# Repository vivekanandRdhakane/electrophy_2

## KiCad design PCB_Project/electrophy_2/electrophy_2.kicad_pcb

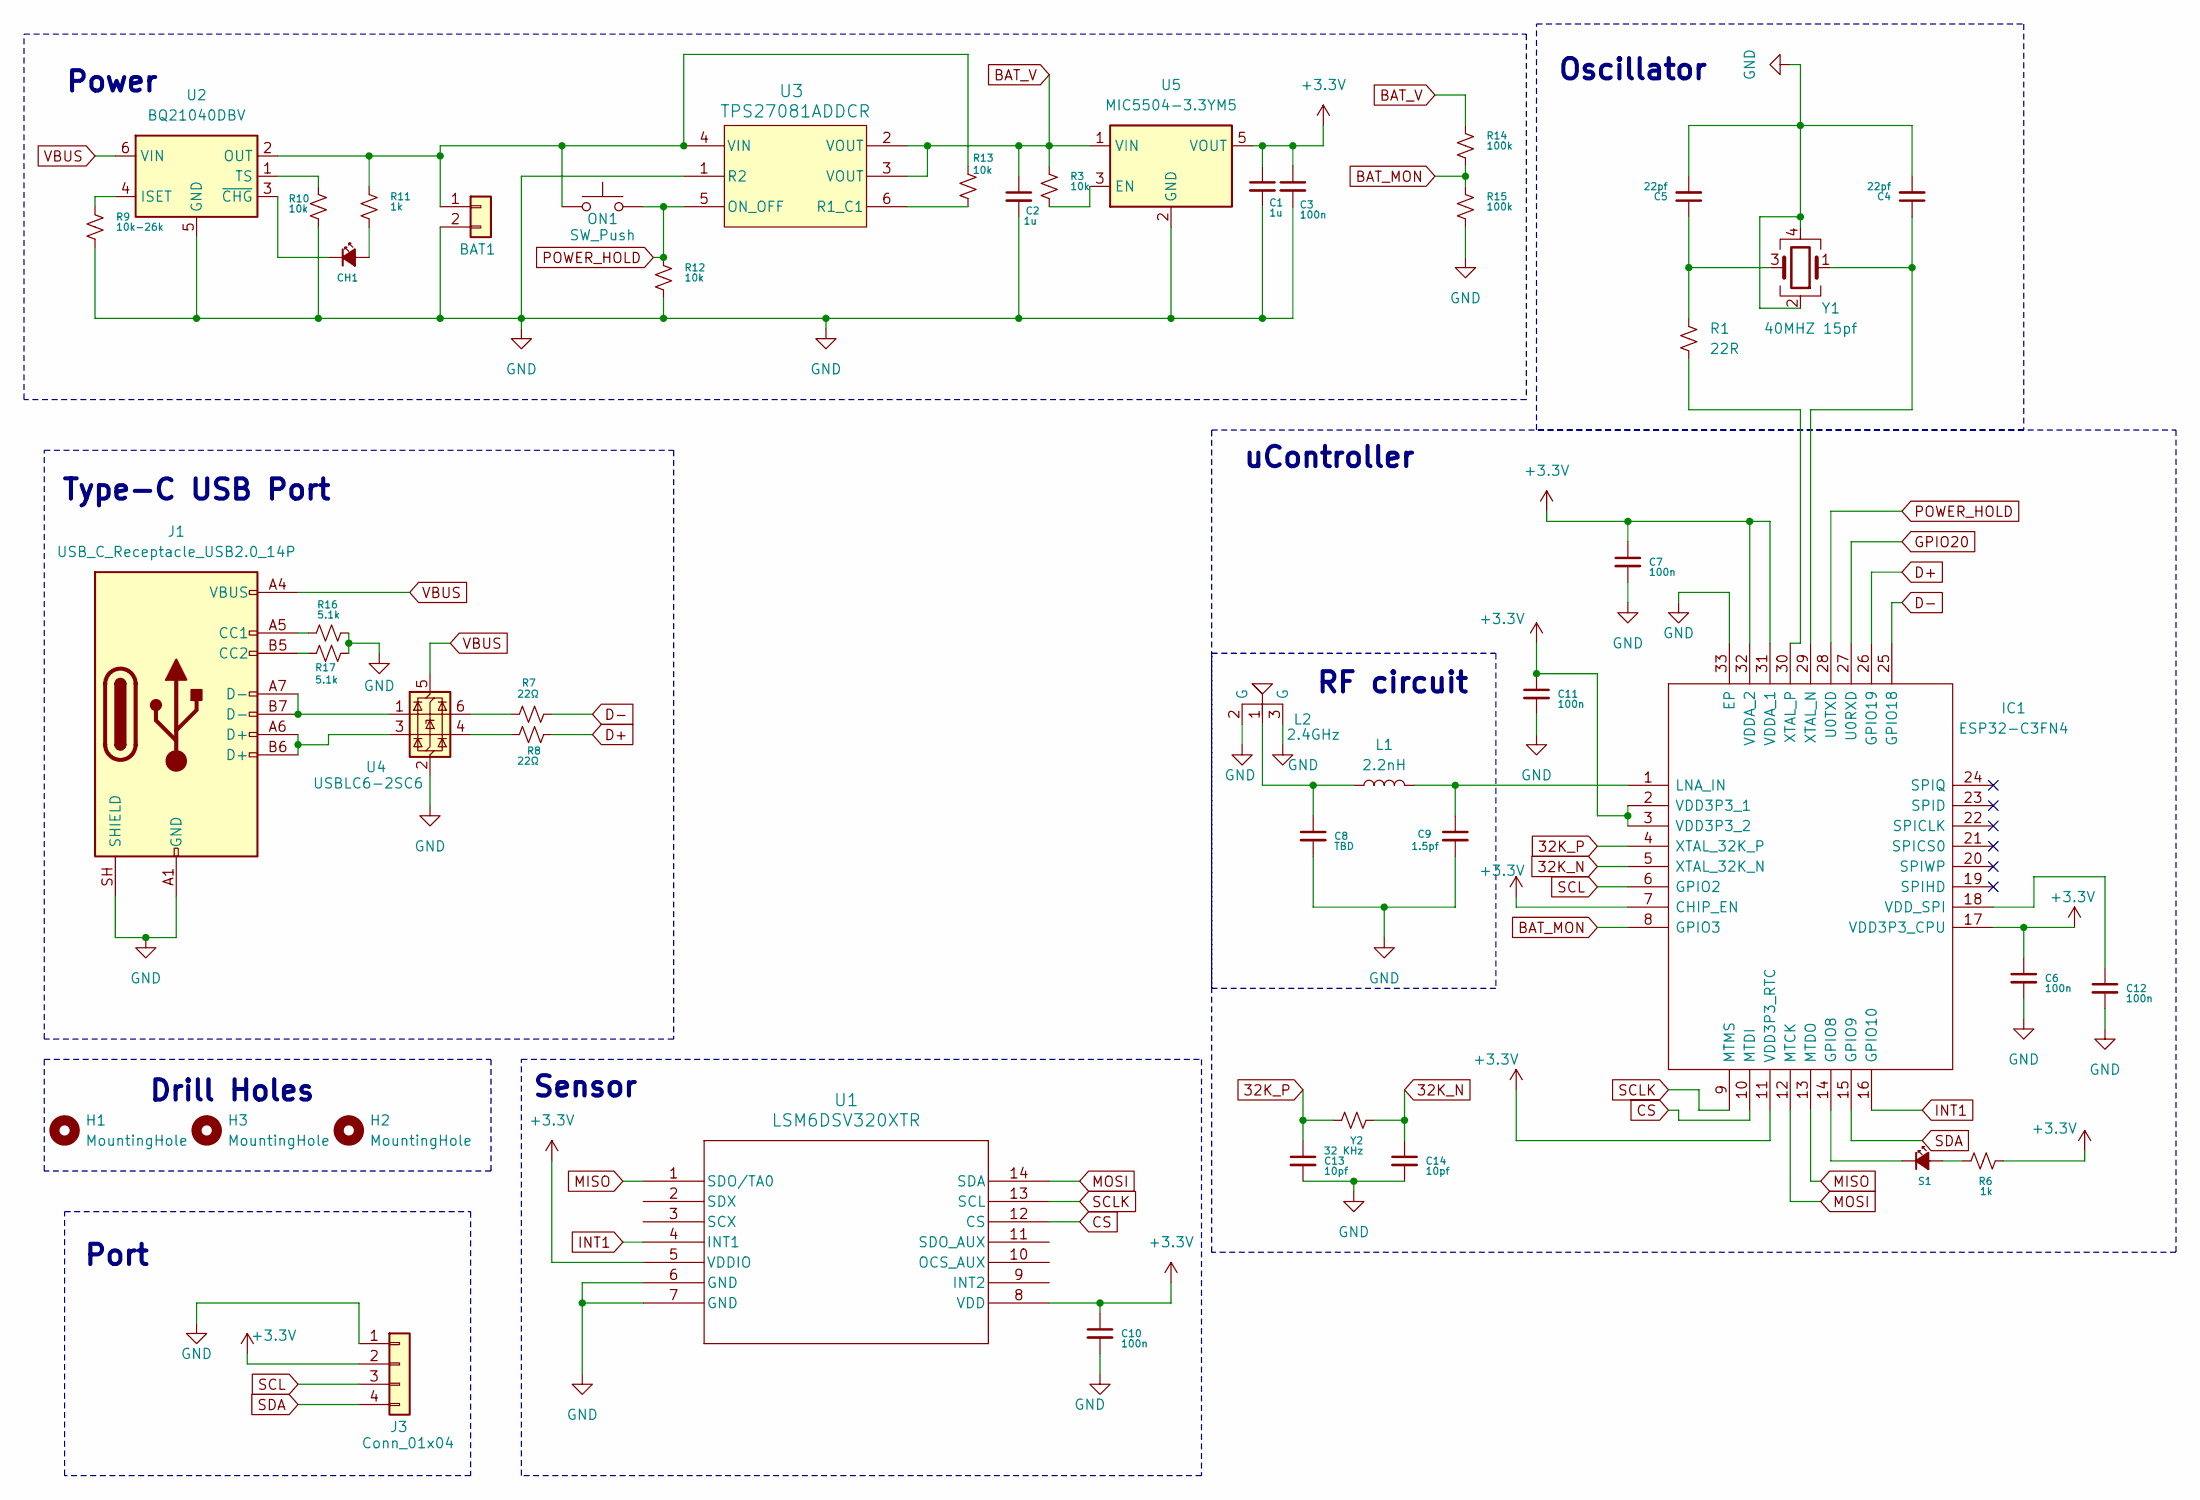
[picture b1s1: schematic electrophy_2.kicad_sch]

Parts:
BAT1: R_1206_3216Metric
C1, C2: 1u; C_0402_1005Metric_Pad0.74x0.62mm_HandSolder
C3, C6, C7, C10, C11, C12: 100n; C_0402_1005Metric_Pad0.74x0.62mm_HandSolder
C4, C5: 22pf; C_0402_1005Metric_Pad0.74x0.62mm_HandSolder
C8: TBD; C_0402_1005Metric
C9: 1.5pf; C_0402_1005Metric
C13, C14: 10pf; C_0402_1005Metric_Pad0.74x0.62mm_HandSolder
CH1: LED_Small_Filled; LED_0402_1005Metric_Pad0.77x0.64mm_HandSolder
H1: MountingHole; MountingHole_2.2mm_M2_Pad_Via
H2, H3: MountingHole; MountingHole_2.2mm_M2
IC1: ESP32-C3FN4; QFN-32-1EP_5x5mm_P0.5mm_EP3.7x3.7mm; Manufacturer_Part_Number ESP32-C3FN4; Mouser Part Number 356-ESP32-C3FN4
J1: USB_C_Receptacle_USB2.0_14P; USB_C_Receptacle_XKB_U262-16XN-4BVC11
J3: Conn_01x04; pogo_pads_4
L1: 2.2nH; L_0402_1005Metric
L2: 2.4GHz; Chip Antenaa INPAQ ACA-5036-A2-CC-S
ON1: SW_Push; SW_SPST_CK_RS282G05A3
R1: 22R; R_0402_1005Metric_Pad0.72x0.64mm_HandSolder
R3, R10, R12, R13: 10k; R_0402_1005Metric_Pad0.72x0.64mm_HandSolder
R6, R11: 1k; R_0402_1005Metric_Pad0.72x0.64mm_HandSolder
R7, R8: 22Ω; R_0402_1005Metric_Pad0.72x0.64mm_HandSolder
R9: 10k-26k; R_0402_1005Metric_Pad0.72x0.64mm_HandSolder
R14, R15: 100k; R_0402_1005Metric_Pad0.72x0.64mm_HandSolder
R16, R17: 5.1k; R_0402_1005Metric_Pad0.72x0.64mm_HandSolder
S1: LED_Small_Filled; LED_0402_1005Metric_Pad0.77x0.64mm_HandSolder
U1: LSM6DSV320XTR; LGA-14L_2p5X3X0p83_STM
U2: BQ21040DBV; SOT-23-6
U3: TPS27081ADDCR; TPS27081ADDCR_N
U4: USBLC6-2SC6; SOT-23-6
U5: MIC5504-3.3YM5; SOT-23-5
Y1: 40MHZ 15pf; Crystal_SMD_3225-4Pin_3.2x2.5mm
Y2: 32 KHz; R_0402_1005Metric_Pad0.72x0.64mm_HandSolder

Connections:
32K_N: C14.1, IC1.5 (XTAL_32K_N), Y2.2
32K_P: C13.1, IC1.4 (XTAL_32K_P), Y2.1
+3.3V: C1.1, C3.1, C6.1, C7.1, C10.1, C11.1, IC1.2 (VDD3P3_1), IC1.3 (VDD3P3_2), IC1.7 (CHIP_EN), IC1.11 (VDD3P3_RTC), IC1.17 (VDD3P3_CPU), IC1.31 (VDDA_1), IC1.32 (VDDA_2), J3.2, R6.2, U1.5 (VDDIO), U1.8 (VDD), U5.5 (VOUT)
BAT_MON: IC1.8 (GPIO3), R14.2, R15.1
BAT_V: C2.1, R3.1, R14.1, U3.2 (VOUT), U3.3 (VOUT), U5.1 (VIN)
CS: IC1.10 (MTDI), U1.12 (CS)
D+: IC1.26 (GPIO19), R8.2
D-: IC1.25 (GPIO18), R7.2
GND: BAT1.2, C1.2, C2.2, C3.2, C4.2, C5.2, C6.2, C7.2, C8.2, C9.2, C10.2, C11.2, C12.2, C13.2, C14.2, IC1.33 (EP), J1.A1 (GND), J1.A12 (GND), J1.B1 (GND), J1.B12 (GND), J1.SH (SHIELD), J3.1, L2.2 (G), L2.3 (G), R9.2, R10.2, R12.2, R15.2, R16.2, R17.2, U1.6 (GND), U1.7 (GND), U2.5 (GND), U3.1 (R2), U4.2 (GND), U5.2 (GND), Y1.2, Y1.4
GPIO20: IC1.27 (U0RXD)
INT1: IC1.16 (GPIO10), U1.4 (INT1)
MISO: IC1.13 (MTDO), U1.1 (SDO/TA0)
MOSI: IC1.12 (MTCK), U1.14 (SDA)
unnamed: BAT1.1, ON1.1, R11.1, R13.1, U2.2 (OUT), U3.4 (VIN)
unnamed: C5.1, R1.1, Y1.3
unnamed: C8.1, L1.1, L2.1
unnamed: CH1.2 (A), R11.2
unnamed: CH1.1 (K), U2.3 (~CHG)
unnamed: IC1.14 (GPIO8), S1.1 (K)
unnamed: C9.1, IC1.1 (LNA_IN), L1.2
unnamed: C12.1, IC1.18 (VDD_SPI)
unnamed: C4.1, IC1.29 (XTAL_N), Y1.1
unnamed: IC1.30 (XTAL_P), R1.2
unnamed: J1.A5 (CC1), R16.1
unnamed: J1.B5 (CC2), R17.1
unnamed: J1.A6 (D+), J1.B6 (D+), U4.3 (I/O2)
unnamed: J1.A7 (D-), J1.B7 (D-), U4.1 (I/O1)
unnamed: R7.1, U4.6 (I/O1)
unnamed: R8.1, U4.4 (I/O2)
unnamed: R6.1, S1.2 (A)
unnamed: R9.1, U2.4 (ISET)
unnamed: R10.1, U2.1 (TS)
unnamed: R13.2, U3.6 (R1_C1)
unnamed: R3.2, U5.3 (EN)
POWER_HOLD: IC1.28 (U0TXD), ON1.2, R12.1, U3.5 (ON_OFF)
SCL: IC1.6 (GPIO2), J3.3
SCLK: IC1.9 (MTMS), U1.13 (SCL)
SDA: IC1.15 (GPIO9), J3.4
VBUS: J1.A4 (VBUS), J1.A9 (VBUS), J1.B4 (VBUS), J1.B9 (VBUS), U2.6 (VIN), U4.5 (VBUS)

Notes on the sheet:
Type-C USB Port
uController
RF circuit
Power
Drill Holes
Sensor
Port
Oscillator

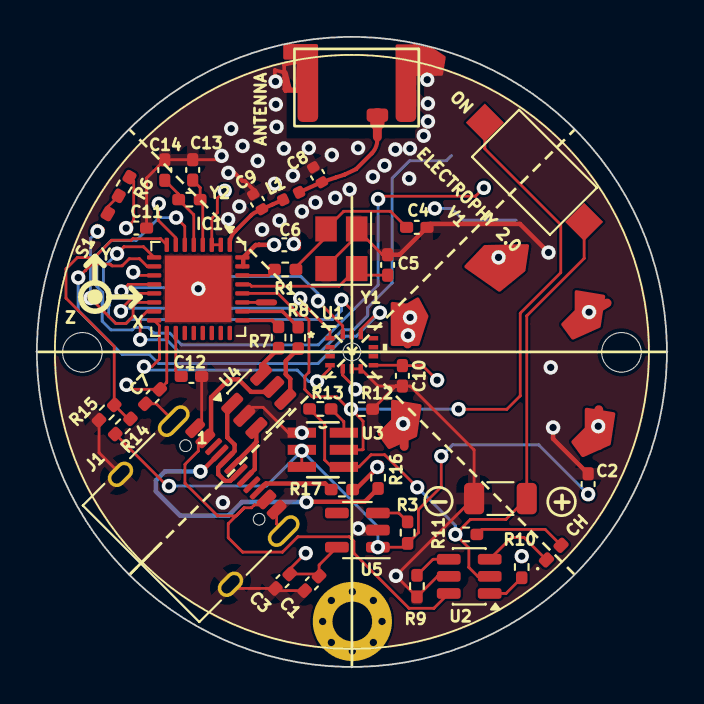
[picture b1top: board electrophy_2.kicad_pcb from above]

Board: 4 copper layers, 35.0 x 35.0 mm, 47 parts (1 on the bottom side), 38 nets.
